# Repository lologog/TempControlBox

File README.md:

# TempControlBox - 🚧 Work in Progress
Device for testing control algorithms and system identification

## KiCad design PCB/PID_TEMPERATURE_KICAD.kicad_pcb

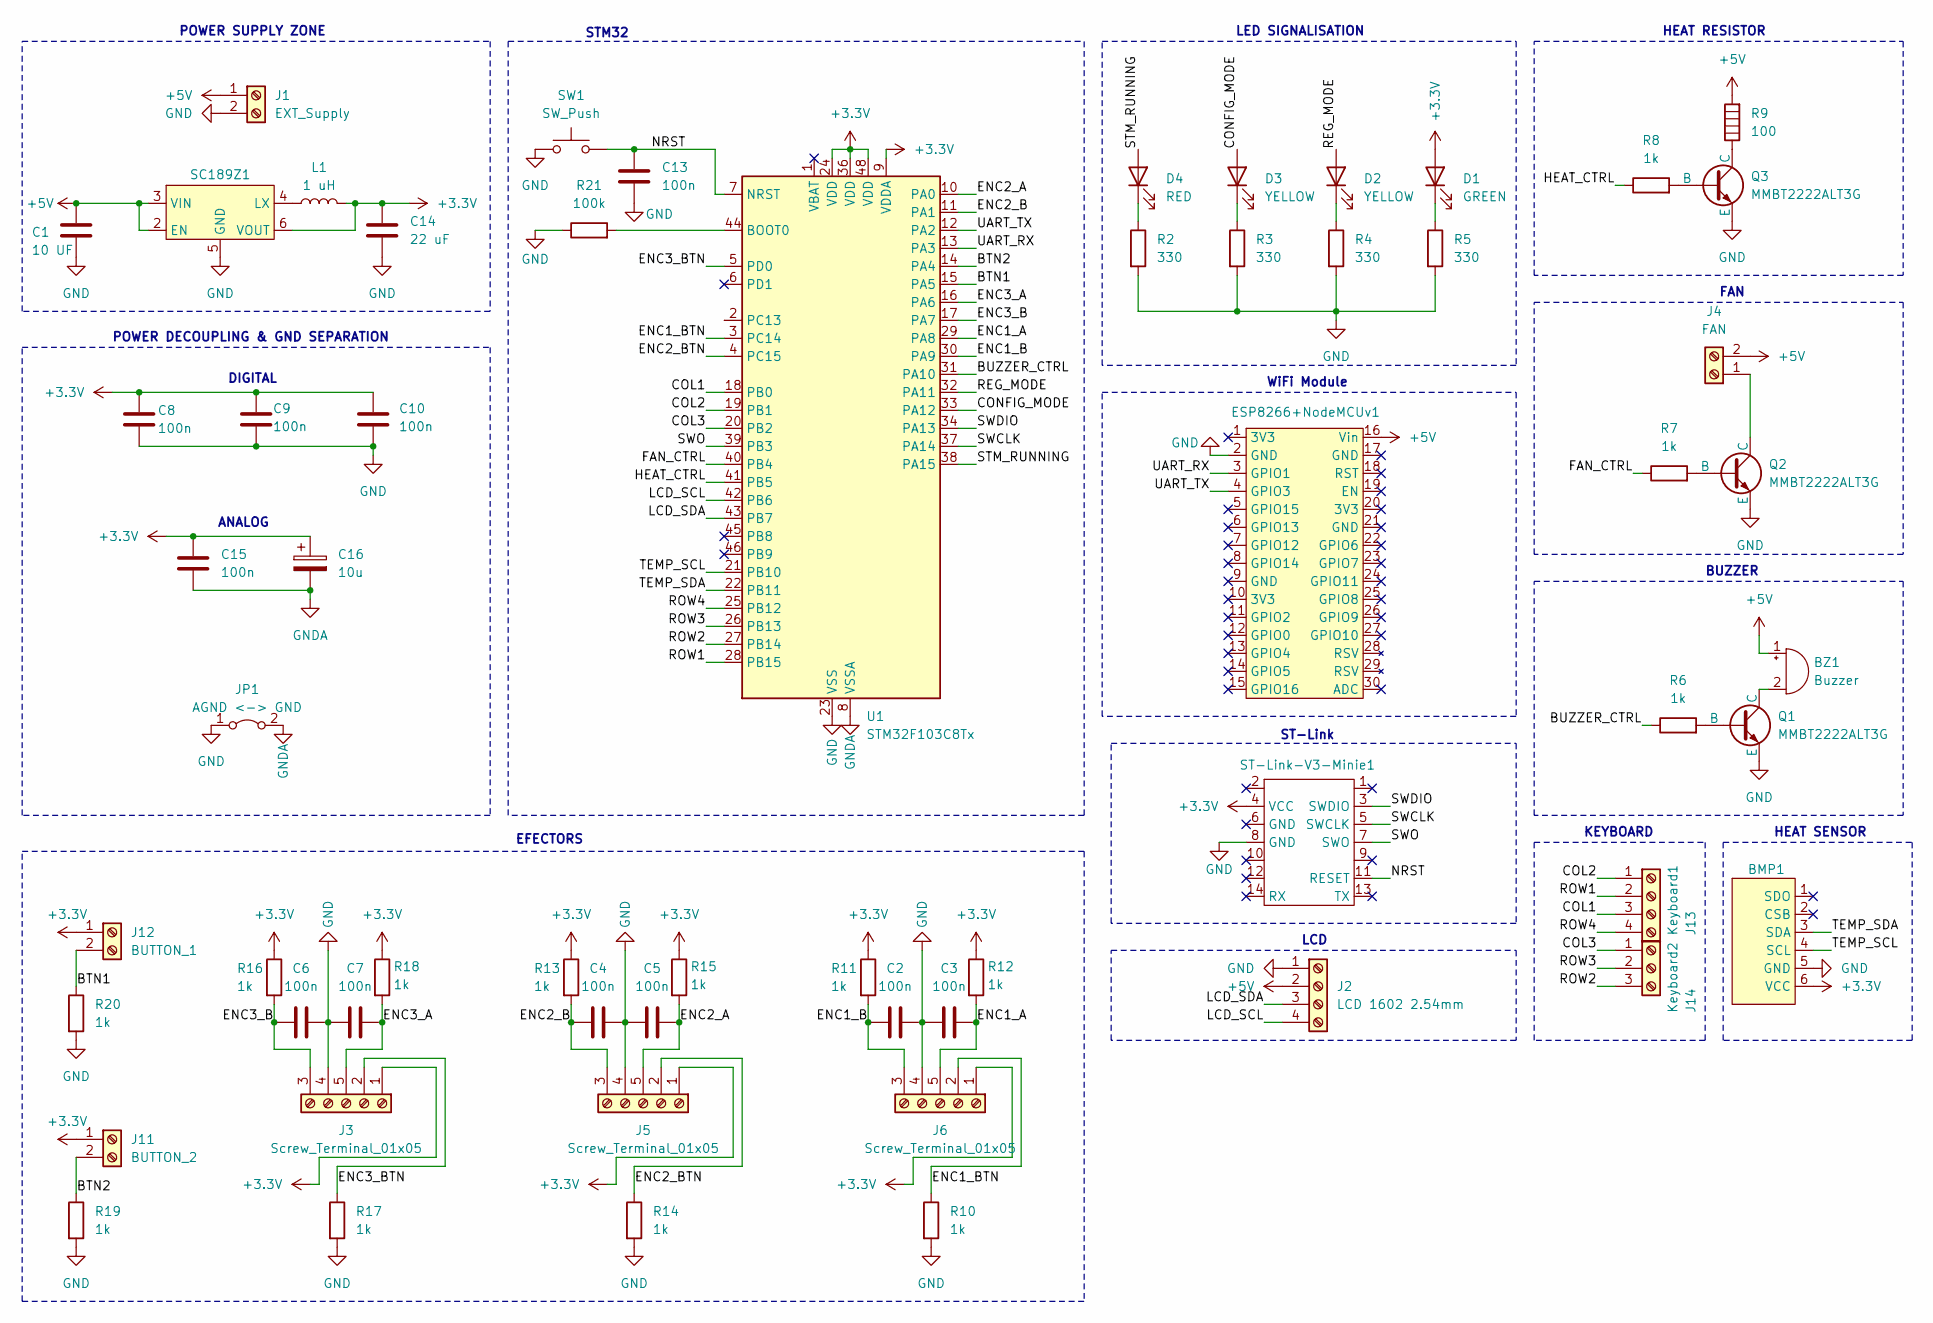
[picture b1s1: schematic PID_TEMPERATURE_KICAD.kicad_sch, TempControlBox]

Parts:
BMP1: BMP280
BZ1: Buzzer; Buzzer_12x9.5RM7.6
C1: 10 UF; C_0805_2012Metric_Pad1.18x1.45mm_HandSolder
C2, C3, C4, C5, C6, C7, C8, C9, C10, C13, C15: 100n; C_0805_2012Metric_Pad1.18x1.45mm_HandSolder
C14: 22 uF; C_0805_2012Metric_Pad1.18x1.45mm_HandSolder
C16: 10u; CP_Radial_D5.0mm_P2.50mm
D1: GREEN; LED_D3.0mm
D2, D3: YELLOW; LED_D3.0mm
D4: RED; LED_D3.0mm
ESP8266+NodeMCUv1: NodeMCU
J1: EXT_Supply; JST_PH_B2B-PH-K_1x02_P2.00mm_Vertical
J2: LCD 1602 2.54mm; JST_PH_B4B-PH-K_1x04_P2.00mm_Vertical
J3, J5, J6: Screw_Terminal_01x05; JST_PH_B5B-PH-K_1x05_P2.00mm_Vertical
J4: FAN; JST_PH_B2B-PH-K_1x02_P2.00mm_Vertical
J11: BUTTON_2; JST_PH_B2B-PH-K_1x02_P2.00mm_Vertical
J12: BUTTON_1; JST_PH_B2B-PH-K_1x02_P2.00mm_Vertical
J13: Keyboard1; JST_PH_B4B-PH-K_1x04_P2.00mm_Vertical
J14: Keyboard2; JST_PH_B3B-PH-K_1x03_P2.00mm_Vertical
JP1: AGND <-> GND; SolderJumper-2_P1.3mm_Bridged2Bar_Pad1.0x1.5mm
L1: 1 uH; R_0805_2012Metric_Pad1.20x1.40mm_HandSolder
Q1, Q2, Q3: MMBT2222ALT3G; SOT-23
R2, R3, R4, R5: 330; R_0805_2012Metric_Pad1.20x1.40mm_HandSolder
R6, R7, R8, R10, R11, R12, R13, R14, R15, R16, R17, R18, R19, R20: 1k; R_0805_2012Metric_Pad1.20x1.40mm_HandSolder
R9: 100; Heat_Resistor
R21: 100k; R_0805_2012Metric_Pad1.20x1.40mm_HandSolder
SC189Z1: TSOT-23-6_HandSoldering
ST-Link-V3-Minie1: PinSocket_2x07_P1.27mm_Vertical
SW1: SW_Push; SW_PUSH_6mm_H4.3mm
U1: STM32F103C8Tx; LQFP-48_7x7mm_P0.5mm

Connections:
+3.3V: BMP1.6 (VCC), C8.1, C9.1, C10.1, C14.1, C15.1, C16.1, D1.2 (A), J3.1, J5.1, J6.1, J11.1, J12.1, L1.2, R11.1, R12.1, R13.1, R15.1, R16.1, R18.1, SC189Z1.6 (VOUT), ST-Link-V3-Minie1.4 (VCC), U1.9 (VDDA), U1.24 (VDD), U1.36 (VDD), U1.48 (VDD)
+5V: BZ1.1 (+), C1.1, ESP8266+NodeMCUv1.16 (Vin), J1.1, J2.2, J4.2, R9.2, SC189Z1.2 (EN), SC189Z1.3 (VIN)
/BTN1: J12.2, R20.1, U1.15 (PA5)
/BTN2: J11.2, R19.1, U1.14 (PA4)
/BUZZER_CTRL: R6.1, U1.31 (PA10)
/COL1: J13.3, U1.18 (PB0)
/COL2: J13.1, U1.19 (PB1)
/COL3: J14.1, U1.20 (PB2)
/CONFIG_MODE: D3.2 (A), U1.33 (PA12)
/ENC1_A: C3.2, J6.5 (Pin_3), R12.2, U1.29 (PA8)
/ENC1_B: C2.1, J6.3 (Pin_5), R11.2, U1.30 (PA9)
/ENC1_BTN: J6.2, R10.1, U1.3 (PC14)
/ENC2_A: C5.2, J5.5 (Pin_3), R15.2, U1.10 (PA0)
/ENC2_B: C4.1, J5.3 (Pin_5), R13.2, U1.11 (PA1)
/ENC2_BTN: J5.2, R14.1, U1.4 (PC15)
/ENC3_A: C7.2, J3.5 (Pin_3), R18.2, U1.16 (PA6)
/ENC3_B: C6.1, J3.3 (Pin_5), R16.2, U1.17 (PA7)
/ENC3_BTN: J3.2, R17.1, U1.5 (PD0)
/FAN_CTRL: R7.1, U1.40 (PB4)
/HEAT_CTRL: R8.1, U1.41 (PB5)
/LCD_SCL: J2.4, U1.42 (PB6)
/LCD_SDA: J2.3, U1.43 (PB7)
/NRST: C13.1, ST-Link-V3-Minie1.11 (RESET), SW1.2, U1.7 (NRST)
/REG_MODE: D2.2 (A), U1.32 (PA11)
/ROW1: J13.2, U1.28 (PB15)
/ROW2: J14.3, U1.27 (PB14)
/ROW3: J14.2, U1.26 (PB13)
/ROW4: J13.4, U1.25 (PB12)
/STM_RUNNING: D4.2 (A), U1.38 (PA15)
/SWCLK: ST-Link-V3-Minie1.5 (SWCLK), U1.37 (PA14)
/SWDIO: ST-Link-V3-Minie1.3 (SWDIO), U1.34 (PA13)
/SWO: ST-Link-V3-Minie1.7 (SWO), U1.39 (PB3)
/TEMP_SCL: BMP1.4 (SCL), U1.21 (PB10)
/TEMP_SDA: BMP1.3 (SDA), U1.22 (PB11)
/UART_RX: ESP8266+NodeMCUv1.3 (GPIO1), U1.13 (PA3)
/UART_TX: ESP8266+NodeMCUv1.4 (GPIO3), U1.12 (PA2)
GND: BMP1.5 (GND), C1.2, C2.2, C3.1, C4.2, C5.1, C6.2, C7.1, C8.2, C9.2, C10.2, C13.2, C14.2, ESP8266+NodeMCUv1.2 (GND), J1.2, J2.1, J3.4, J5.4, J6.4, JP1.1 (A), Q1.2 (E), Q2.2 (E), Q3.2 (E), R2.2, R3.2, R4.2, R5.2, R10.2, R14.2, R17.2, R19.2, R20.2, R21.1, SC189Z1.5 (GND), ST-Link-V3-Minie1.8 (GND), SW1.1, U1.23 (VSS), U1.35 (VSS), U1.47 (VSS)
GNDA: C15.2, C16.2, JP1.2 (B), U1.8 (VSSA)
unnamed: BZ1.2 (-), Q1.3 (C)
unnamed: D1.1 (K), R5.1
unnamed: D2.1 (K), R4.1
unnamed: D3.1 (K), R3.1
unnamed: D4.1 (K), R2.1
unnamed: J4.1, Q2.3 (C)
unnamed: Q1.1 (B), R6.2
unnamed: Q2.1 (B), R7.2
unnamed: Q3.1 (B), R8.2
unnamed: Q3.3 (C), R9.1
unnamed: L1.1, SC189Z1.4 (LX)
unnamed: R21.2, U1.44 (BOOT0)

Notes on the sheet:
HEAT RESISTOR
ST-Link
EFECTORS
LCD
HEAT SENSOR
POWER DECOUPLING & GND SEPARATION
WiFi Module
BUZZER
ANALOG
STM32
LED SIGNALISATION
FAN
KEYBOARD
DIGITAL
POWER SUPPLY ZONE

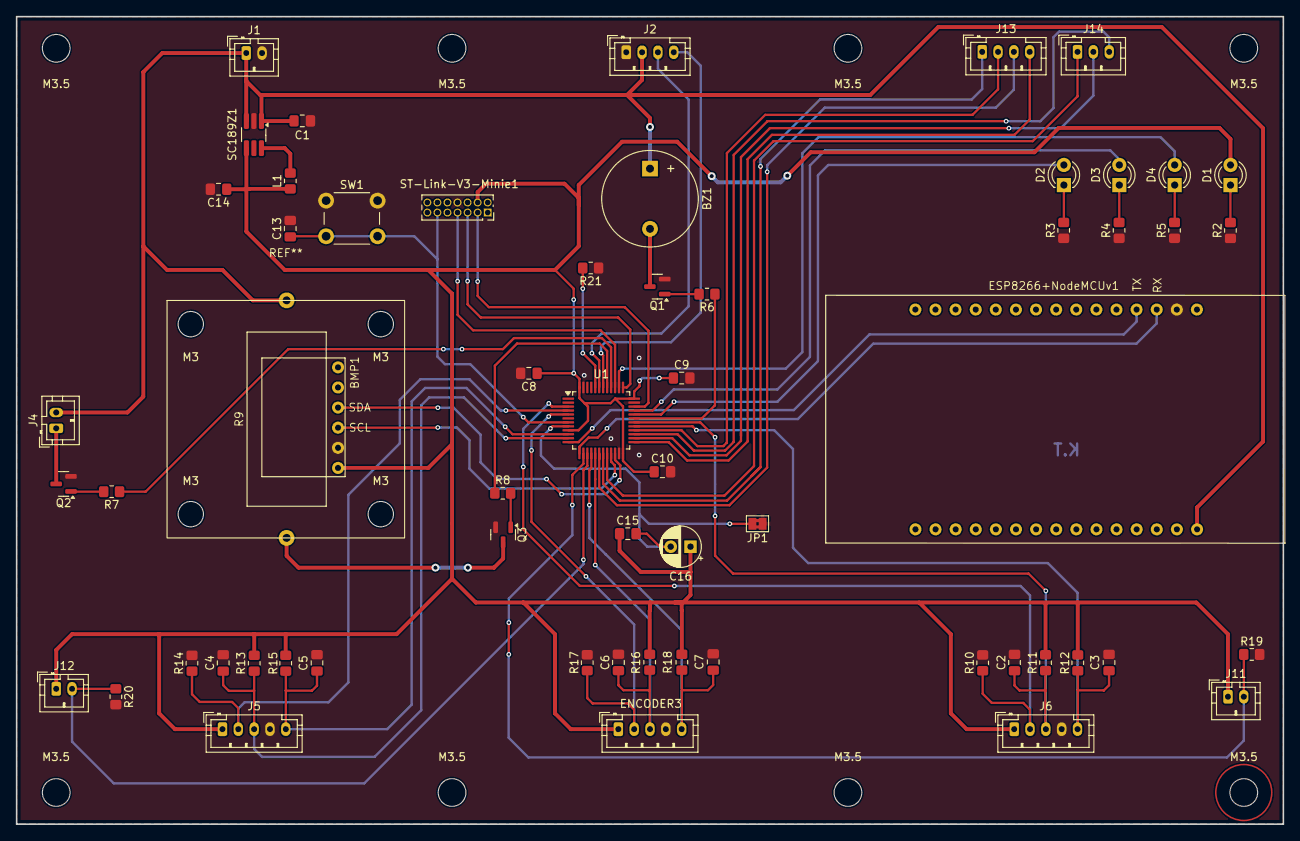
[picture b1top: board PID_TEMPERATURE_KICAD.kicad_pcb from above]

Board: 2 copper layers, 160.0 x 102.0 mm, 72 parts (0 on the bottom side), 50 nets.

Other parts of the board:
M3, M3#2, M3#3, M3#4: MountingHole_3.2mm_M3
M3.5, M3.5#2, M3.5#3, M3.5#4, M3.5#5, M3.5#6, M3.5#7, M3.5#8: MountingHole_3.5mm

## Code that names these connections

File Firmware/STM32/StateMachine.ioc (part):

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Mcu.Name=STM32F103C(8-B)Tx
Mcu.Package=LQFP48
Mcu.UserName=STM32F103C8Tx
PA0-WKUP.GPIOParameters=GPIO_Label
PA0-WKUP.GPIO_Label=ENC2_A
PA0-WKUP.Signal=S_TIM2_CH1_ETR
PA1.GPIOParameters=GPIO_Label
PA1.GPIO_Label=ENC2_B
PA1.Signal=S_TIM2_CH2
PA10.GPIOParameters=GPIO_PuPd,GPIO_Label
PA10.GPIO_Label=BUZZER_CTRL
PA10.GPIO_PuPd=GPIO_PULLDOWN
PA10.Signal=GPIO_Output
PA11.GPIOParameters=GPIO_PuPd,GPIO_Label
PA11.GPIO_Label=REG_MODE
PA11.GPIO_PuPd=GPIO_PULLDOWN
PA11.Signal=GPIO_Output
PA12.GPIOParameters=GPIO_PuPd,GPIO_Label
PA12.GPIO_Label=CONFIG_MODE
PA12.GPIO_PuPd=GPIO_PULLDOWN
PA12.Signal=GPIO_Output
PA13.GPIOParameters=GPIO_Label
PA13.GPIO_Label=SWDIO
PA13.Mode=Serial_Wire
PA13.Signal=SYS_JTMS-SWDIO
PA14.GPIOParameters=GPIO_Label
PA14.GPIO_Label=SWCLK
PA14.Mode=Serial_Wire
PA14.Signal=SYS_JTCK-SWCLK
PA15.GPIOParameters=GPIO_PuPd,GPIO_Label
PA15.GPIO_Label=STM_RUNNING
PA15.GPIO_PuPd=GPIO_PULLDOWN
PA15.Signal=GPIO_Output
PA2.GPIOParameters=GPIO_Label
PA2.GPIO_Label=UART_TX
PA2.Mode=Asynchronous
PA2.Signal=USART2_TX
PA3.GPIOParameters=GPIO_Label
PA3.GPIO_Label=UART_RX
PA3.Mode=Asynchronous
PA3.Signal=USART2_RX
PA4.GPIOParameters=GPIO_Label
PA4.GPIO_Label=BTN2
PA4.Signal=GPXTI4
PA5.GPIOParameters=GPIO_PuPd,GPIO_Label
PA5.GPIO_Label=BTN1
PA5.GPIO_PuPd=GPIO_PULLDOWN
PA5.Signal=GPIO_Input
PA6.GPIOParameters=GPIO_Label
PA6.GPIO_Label=ENC3_A
PA6.Signal=S_TIM3_CH1
PA7.GPIOParameters=GPIO_Label
PA7.GPIO_Label=ENC3_B
PA7.Signal=S_TIM3_CH2
PA8.GPIOParameters=GPIO_Label
PA8.GPIO_Label=ENC1_A
PA8.Signal=S_TIM1_CH1
PA9.GPIOParameters=GPIO_Label
PA9.GPIO_Label=ENC1_B
PA9.Signal=S_TIM1_CH2
PB0.GPIOParameters=GPIO_PuPd,GPIO_Label
PB0.GPIO_Label=COL1
PB0.GPIO_PuPd=GPIO_PULLUP
PB0.Signal=GPIO_Input
PB1.GPIOParameters=GPIO_PuPd,GPIO_Label
PB1.GPIO_Label=COL2
PB1.GPIO_PuPd=GPIO_PULLUP
PB1.Signal=GPIO_Input
PB10.GPIOParameters=GPIO_Label
PB10.GPIO_Label=TEMP_SCL
PB10.Mode=I2C
PB10.Signal=I2C2_SCL
PB11.GPIOParameters=GPIO_Label
PB11.GPIO_Label=TEMP_SDA
PB11.Mode=I2C
PB11.Signal=I2C2_SDA
PB12.GPIOParameters=GPIO_PuPd,GPIO_Label
PB12.GPIO_Label=ROW4
PB12.GPIO_PuPd=GPIO_PULLUP
PB12.Signal=GPIO_Output
PB13.GPIOParameters=GPIO_PuPd,GPIO_Label
PB13.GPIO_Label=ROW3
PB13.GPIO_PuPd=GPIO_PULLUP
PB13.Signal=GPIO_Output
PB14.GPIOParameters=GPIO_PuPd,GPIO_Label
PB14.GPIO_Label=ROW2
PB14.GPIO_PuPd=GPIO_PULLUP
PB14.Signal=GPIO_Output
PB15.GPIOParameters=GPIO_PuPd,GPIO_Label
PB15.GPIO_Label=ROW1
PB15.GPIO_PuPd=GPIO_PULLUP
PB15.Signal=GPIO_Output
PB2.GPIOParameters=GPIO_PuPd,GPIO_Label
PB2.GPIO_Label=COL3
PB2.GPIO_PuPd=GPIO_PULLUP
PB2.Signal=GPIO_Input
PB4.GPIOParameters=GPIO_PuPd,GPIO_Label
PB4.GPIO_Label=FAN_CTRL
PB4.GPIO_PuPd=GPIO_PULLDOWN
PB4.Signal=GPIO_Output
PB5.GPIOParameters=GPIO_PuPd,GPIO_Label
PB5.GPIO_Label=HEAT_CTRL
PB5.GPIO_PuPd=GPIO_PULLDOWN
PB5.Signal=GPIO_Output
PB6.GPIOParameters=GPIO_Label
PB6.GPIO_Label=LCD_SCL
PB6.Mode=I2C
PB6.Signal=I2C1_SCL
PB7.GPIOParameters=GPIO_Label
PB7.GPIO_Label=LCD_SDA
PB7.Mode=I2C
PB7.Signal=I2C1_SDA
PC14-OSC32_IN.GPIOParameters=GPIO_PuPd,GPIO_Label
PC14-OSC32_IN.GPIO_Label=ENC1_BTN
PC14-OSC32_IN.GPIO_PuPd=GPIO_PULLDOWN
PC14-OSC32_IN.Signal=GPIO_Input
PC15-OSC32_OUT.GPIOParameters=GPIO_PuPd,GPIO_Label
PC15-OSC32_OUT.GPIO_Label=ENC2_BTN
PC15-OSC32_OUT.GPIO_PuPd=GPIO_PULLDOWN
PC15-OSC32_OUT.Signal=GPIO_Input
PD0-OSC_IN.GPIOParameters=GPIO_PuPd,GPIO_Label
PD0-OSC_IN.GPIO_Label=ENC3_BTN
PD0-OSC_IN.GPIO_PuPd=GPIO_PULLDOWN
PD0-OSC_IN.Signal=GPIO_Input
board=custom

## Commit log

2025-03-03 project: add 3D render of the PCB to images
2025-03-03 project: add stm32 StateMachine project files
2025-03-03 project: add PCB and schematic to PCB folder
2025-03-03 project: fixing LED color description
2025-03-04 project: add working LEDs
2025-03-04 project: add 2 buttons to the project
2025-03-04 Revert "Merge pull request #1 from lologog/dev"
    This reverts commit 592201721d847cee020b1f18eabaf14be8bc48c8, reversing
    changes made to 8926a7ebba7f131fc6c6466d1f3102db8be0bb79.
2025-03-04 project: add 3 encoder buttons to the project
2025-03-04 project: created new LCD library and working initialization, sendchar and sendcommand functions
2025-03-04 project: add working LCD_SendString function
2025-03-04 project: add working LCD_clear function
2025-03-04 project: add LCD_SetCursor function and now whole LCD library is finished
2025-03-04 project: code is ready for merging
2025-03-04 project: fixing conflicts during merging to main
2025-03-04 project: add working Keyboard library and pin setup
2025-03-04 README: add 3D render photo
2025-03-05 project: dev ready for merge
2025-03-05 project: add PCB and Box photos to the Images folder
2025-03-05 README: add PCB and Box photos
2025-03-06 project: add working encoders
2025-03-06 project: commit in main with clean code for encoders
2025-03-06 project: add regulation effectors
2025-03-06 project: add temperature reading via I2C with self-created libraries
2025-03-06 project: small reorganisation in LCD library
2025-03-06 project: dev ready to merge
2025-03-07 project: add UART configuration to STM
2025-03-07 project: add logic.h and logic.c files with main state machine logic and first state is working
2025-03-07 project: add reset program interrupt button
2025-03-09 Project: add LED that shows that STM is running correctly
2025-03-09 Project: fixing LED names order
2025-03-09 Project: aesthetic correctons in STATE_INIT
2025-03-09 Project: started working on STATE_REG_TYPE
2025-03-15 Project: add WRONG NUMBER information if wrong number is chosen
2025-03-15 Project: small improvements in error message code
2025-03-15 Project: added new state for bang bang configuration
2025-03-21 Project: fixed bug with floating 'wrong number' after 2 sec
2025-03-21 Project: Added basic functionality of BANG BANG TEMP CONF state
2025-03-21 Project: added automatically writing dot after second digit in BANG BANG TEMP CONF
2025-03-21 Project: fixed bug and now user has to enter all digits before going into next state
2025-03-21 Project: removing automatically dot - too much uncomfortable
2025-03-28 README: add work in progress information
2025-09-07 Project: Convert from STM32CubeIDE into VSCode
2025-09-07 Logic: add initial state
2025-09-07 Project: add state to choose control type, upgrade keyboard library and handle STM ok LED in main
